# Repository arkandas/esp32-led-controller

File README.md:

# ESP32 LED Controller 💡

A custom ESP32-based controller for WS2812B/SK6812/WS2814 LED strips with web interface and Alexa integration.

> **Latest Version:** V2 includes 24V RGBW support (WS2814), temperature/humidity monitoring, and enhanced status LEDs.

## Versions

### Version 2
✅ Released - Latest version in `main` branch

### Version 1
✅ Released - Tagged as `v1.0.0`

---

## Version 2 Documentation

The following documentation applies to **Version 2** of the project. All files are located in the `v2/` directory.

### ✨ Features

- 🎨 **Web Interface** - Real-time control with environment monitoring
- 🗣️ **Alexa Integration** - Voice control support
- 🔘 **Physical Buttons** - Manual brightness/mode control
- 🌈 **Multiple Effects** - Rainbow, chase, breathing animations
- 📱 **Custom Colors** - Full RGBW color picker
- 🌡️ **Temperature & Humidity** - AHT20 sensor for environment monitoring
- 💡 **Status LEDs** - 3x RGB status indicators (Power, WiFi, Strip)
- ⚡ **24V RGBW Support** - WS2814 LED strips with dedicated white channel

### 📁 Project Structure

```
v2/
├── code/                      # Arduino code & web interface
│   └── esp32-ws2814/          # WS2814 (RGBW) version
│       ├── data/              # Web interface files
│       │   ├── index.html     # Main web UI
│       │   ├── style.css      # Styling
│       │   └── app.js         # JavaScript controls
│       └── esp32-ws2814.ino   # Arduino sketch
├── kicad/                     # KiCad PCB project files
└── assets/                    # Board photos & schematics
```

### 🚀 Quick Start

#### Prerequisites

1. **Arduino IDE** with ESP32 support
2. **Required Libraries:**
   - Adafruit NeoPixel (for WS2814 RGBW)
   - FastLED (for status LEDs)
   - FauxmoESP (Alexa integration)
   - AsyncTCP & ESPAsyncWebServer (ESP32 versions)
   - LittleFS (file system)
   - Adafruit AHTX0 (temperature sensor)

#### Installation

1. **Add ESP32 Board Support:**
   ```
   File → Preferences → Additional Board Manager URLs:
   https://raw.githubusercontent.com/espressif/arduino-esp32/gh-pages/package_esp32_index.json
   ```

2. **Board Configuration:**
   - Board: "ESP32S3 Dev Module"
   - Flash Size: "8MB"
   - Partition Scheme: "8M with spiffs (3MB APP/1.5MB SPIFFS)"

3. **Install Libraries** via Library Manager

#### Upload Process

1. **Configure Settings** in the `.ino` file:
   ```cpp
   const char* ssid = "Your_WiFi_Network";
   const char* password = "Your_WiFi_Password";
   #define DEVICE_NAME "Your_Alexa_Device_Name"
   #define WIFI_HOSTNAME "Your_Device_Hostname"
   #define WEB_SERVER_PORT 8080  // Your preferred port
   #define NUM_LEDS 60  // Your LED count
   ```

2. **Upload Web Files:**
   - Install [Arduino LittleFS Upload](https://github.com/earlephilhower/arduino-littlefs-upload) plugin
   - Place the `data` folder in your sketch directory
   - Use: Cmd + Shift + P, then select "Upload LittleFS to Pico/ESP8266/ESP32"

3. **Upload Arduino Sketch** normally

#### Programming via USB

The v2 board uses an **ESP32-S3** with built-in USB - no need for an external USB-to-serial adapter.

**USB Connection:**
- Connect a USB-C cable directly to the ESP32-S3's USB port
- The board will show up as a serial device on your computer

**Arduino IDE USB Configuration:**

To get USB UART working on the Serial Monitor:

1. **Board Settings (Tools menu):**
   - Board: `ESP32S3 Dev Module`
   - USB CDC On Boot: `Enabled` ⚠️ **Important for Serial Monitor**
   - USB Mode: `Hardware CDC and JTAG`
   - Upload Mode: `UART0 / Hardware CDC`
   - Flash Size: `8MB`
   - Partition Scheme: `8M with spiffs (3MB APP/1.5MB SPIFFS)`
   - Upload Speed: `921600` (or lower if uploads fail)

2. **Port Selection:**
   - After connecting USB, select the port showing as ESP32-S3 in Tools → Port
   - macOS: Usually appears as `/dev/cu.usbmodem*`
   - Windows: Usually appears as `COM*`
   - Linux: Usually appears as `/dev/ttyACM*`

**USB CDC On Boot Explained:**
- When `Enabled`, the Serial Monitor will work over USB immediately after boot
- This allows you to see debug output using `Serial.println()` without additional hardware
- The board will enumerate as a USB serial device (CDC - Communications Device Class)

**First-Time Programming:**
1. Connect the board via USB-C
2. The ESP32-S3 should automatically enter bootloader mode when uploading
3. If upload fails, try:
   - Press and hold the `BOOT` button (if available on your board)
   - Click Upload in Arduino IDE
   - Release `BOOT` button when upload starts
4. Open Serial Monitor (Ctrl/Cmd + Shift + M) at `115200` baud to see output

**Troubleshooting:**
- **Port not appearing:** Try a different USB cable (must support data, not just power)
- **Upload fails:** Lower the upload speed to `460800` or `115200`
- **Serial Monitor shows gibberish:** Ensure baud rate is set to `115200` and USB CDC On Boot is enabled

### 🔌 Hardware Connections

| ESP32 Pin | Connection |
|-----------|------------|
| GPIO 40   | WS2814 LED Strip Data |
| GPIO 41   | Status LEDs (3x SK6805-EC20) |
| GPIO 1    | I2C SCL (AHT20 Sensor) |
| GPIO 2    | I2C SDA (AHT20 Sensor) |
| GPIO 4-7  | Control Buttons |

### 🌐 Usage

After successful upload:

1. **WiFi Connection:** Status LEDs flash yellow (5x) when connected
2. **Web Interface:** Visit `http://[ESP32_IP]:8080` (or your configured port)

3. **Alexa:** Say "Alexa, turn on [your device name]"
4. **Buttons:** Physical controls for power/brightness/modes

### 🎛️ Controls

- **Power Button:** Long press (0.5s) to toggle on/off
- **Brightness:** ± buttons adjust in 10% steps
- **Mode Button:** Cycle through colors and effects
- **Web Interface:** Real-time RGBW control, effects, and environment monitoring

### 💡 Status LEDs

The board features 3 RGB status LEDs:
- **LED 1 (Power):** Always green when powered
- **LED 2 (WiFi):** Green when connected, Red when disconnected, Yellow during errors
- **LED 3 (Strip):** Green when strip is on, Red when off

### ⚡ Hardware

Custom PCB design includes:
- ESP32-S3-WROOM-1 (8MB Flash)
- SN74AHCT125 level shifter (3.3V → 5V for WS2814)
- LM1117S-3.3 voltage regulator
- 3x SK6805-EC20 RGB status LEDs
- AHT20 temperature & humidity sensor
- 4 control buttons
- 2.5mm barrel jack power input (24V for WS2814)

### 🔧 Key Differences from V1

- **RGBW Support:** Dedicated white channel for better white light quality
- **24V LED Strips:** Uses WS2814 instead of WS2812B/SK6812
- **Environment Monitoring:** Built-in AHT20 temperature and humidity sensor
- **Improved Status LEDs:** 3x addressable RGB LEDs instead of single common anode LED
- **Enhanced Web Interface:** Shows temperature, humidity, and more device information
- **Configurable Port:** Web server port can be customized

---

## Version 1 Documentation

The following documentation applies to **Version 1** of the project. All files are located in the `v1/` directory.

### ✨ Features

- 🎨 **Web Interface** - Real-time control via browser
- 🗣️ **Alexa Integration** - Voice control support
- 🔘 **Physical Buttons** - Manual brightness/mode control
- 🌈 **Multiple Effects** - Rainbow, chase, breathing animations
- 📱 **Custom Colors** - Full RGB color picker
- 🔧 **Two LED Types** - WS2812B (RGB) and SK6812 (RGBW) support

### 📁 Project Structure

```
v1/
├── code/                       # Arduino code & web interface
│   ├── esp32-ws2812b/          # WS2812B (RGB) version
│   │   ├── data/               # Web interface files
│   │   │   ├── index.html      # Main web UI
│   │   │   ├── style.css       # Styling
│   │   │   └── app.js          # JavaScript controls
│   │   └── esp32-ws2812b.ino   # Arduino sketch
│   └── esp32-sk6812/           # SK6812 (RGBW) version
│       ├── data/               # Web interface files
│       └── esp32-sk6812.ino    # Arduino sketch
├── kicad/                      # KiCad PCB project files
├── gerbers/                    # Manufacturing files
├── datasheets/                 # Component datasheets
├── ibom/                       # Interactive BOM
└── assets/                     # Board photos
```

### 🚀 Quick Start

#### Prerequisites

1. **Arduino IDE** with ESP32 support
2. **Required Libraries:**
   - FastLED (for WS2812B) or Adafruit NeoPixel (for SK6812)
   - FauxmoESP (Alexa integration)
   - AsyncTCP & ESPAsyncWebServer (ESP32 versions)
   - LittleFS (file system)

#### Installation

1. **Add ESP32 Board Support:**
   ```
   File → Preferences → Additional Board Manager URLs:
   https://raw.githubusercontent.com/espressif/arduino-esp32/gh-pages/package_esp32_index.json
   ```

2. **Board Configuration:**
   - Board: "ESP32S3 Dev Module"
   - Flash Size: "8MB"
   - Partition Scheme: "8M with spiffs (3MB APP/1.5MB SPIFFS)"

3. **Install Libraries** via Library Manager

4. **Choose Your LED Type:**
   - `v1/code/esp32-ws2812b/` for standard RGB strips
   - `v1/code/esp32-sk6812/` for RGBW strips with dedicated white channel

#### Upload Process

1. **Configure Settings** in the `.ino` file:
   ```cpp
   const char* ssid = "Your_WiFi_Network";
   const char* password = "Your_WiFi_Password";
   #define DEVICE_NAME "Bedroom Lights"
   #define NUM_LEDS 60  // Your LED count
   ```

2. **Upload Web Files:**
   - Install [Arduino LittleFS Upload](https://github.com/earlephilhower/arduino-littlefs-upload) plugin
   - Place the `data` folder in your sketch directory
   - Use: Cmd + Shift + P, then select "Upload LittleFS to Pico/ESP8266/ESP32"

3. **Upload Arduino Sketch** normally

### 🔌 Hardware Connections

| ESP32 Pin | Connection |
|-----------|------------|
| GPIO 2    | LED Strip Data |
| GPIO 17   | Status LED (Red) |
| GPIO 16   | Status LED (Green) |
| GPIO 18   | Status LED (Blue) |
| GPIO 4-7  | Control Buttons |

### 🌐 Usage

After successful upload:

1. **WiFi Connection:** Board flashes blue → yellow (5x) when connected
2. **Web Interface:** Visit `http://[ESP32_IP]:8080`

3. **Alexa:** Say "Alexa, turn on bedroom lights"
4. **Buttons:** Physical controls for power/brightness/modes

### 🎛️ Controls

- **Power Button:** Long press (0.5s) to toggle on/off
- **Brightness:** ± buttons adjust in 10% steps
- **Mode Button:** Cycle through colors and effects
- **Web Interface:** Real-time RGB control and effects

### 📖 Blog Post

Read the full build story and PCB design process for V1: [ESP32 LED Controller](https://arkandas.com/blog/esp32_led_controller)

### ⚡ Hardware

Custom PCB design includes:
- ESP32-S3-WROOM-1 (8MB Flash)
- SN74AHCT125 level shifter (3.3V → 5V)
- LM1117S-3.3 voltage regulator
- Common anode status LED
- 4 control buttons
- 2.5mm barrel jack power input

### 🛠️ Development

The web interface uses vanilla JavaScript with no external dependencies. All files are served from ESP32's LittleFS for fast loading and offline operation.

## 📄 License

This project is licensed under the MIT License - see the [LICENSE](LICENSE) file for details.

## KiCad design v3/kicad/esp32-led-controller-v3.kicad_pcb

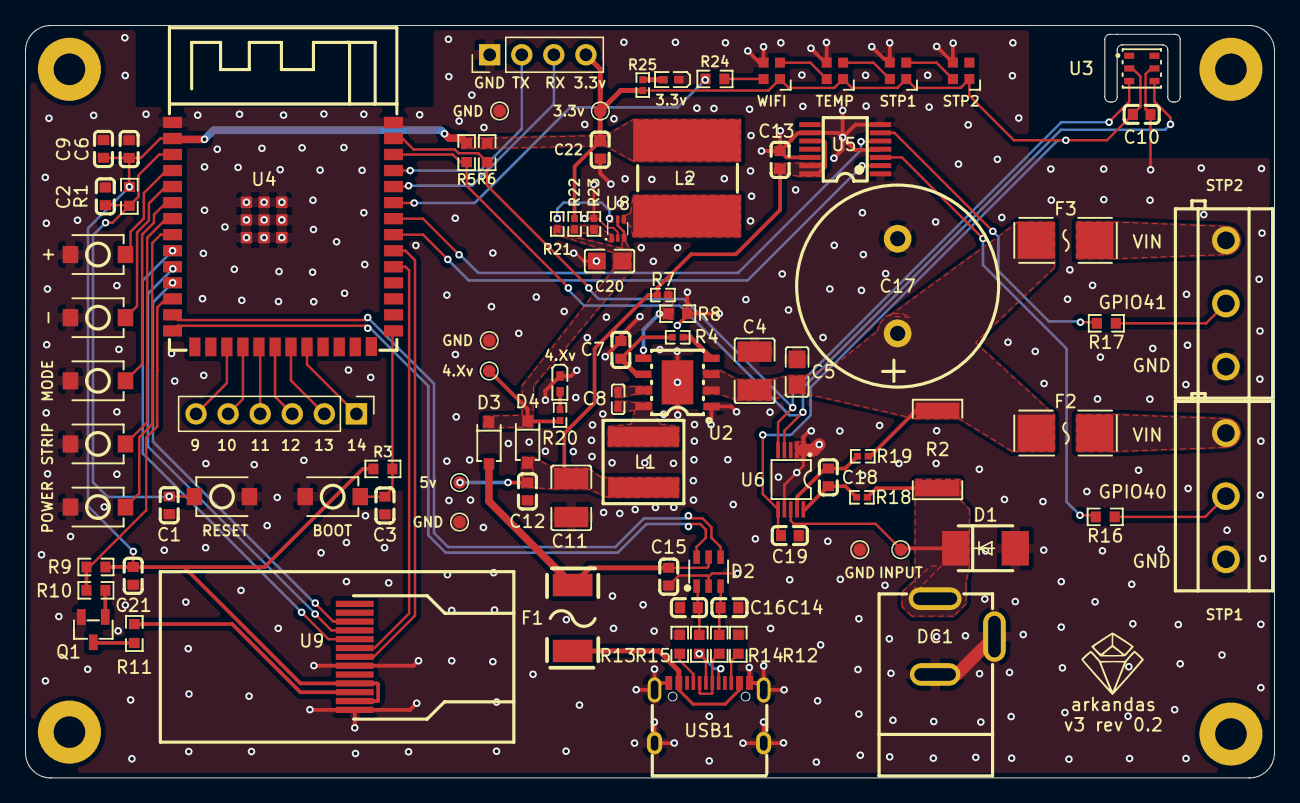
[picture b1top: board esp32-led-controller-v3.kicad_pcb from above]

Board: 2 copper layers, 98.9 x 59.6 mm, 95 parts (0 on the bottom side), 67 nets.

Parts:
3.3v: 3.3v; TestPoint_Pad_D1.0mm
3.3v#2, 4.Xv#2: GREEN_PWR; LED0402-R-RD_GREEN
4.Xv: 4.Xv; TestPoint_Pad_D1.0mm
5v: 5v; TestPoint_Pad_D1.0mm
+: +; SW-SMD_L3.9-W3.0-P4.45
-: -; SW-SMD_L3.9-W3.0-P4.45
C1, C3, C9, C10, C12, C13, C15, C18, C19, C21: 0.1uF; C0603
C2, C7: 1uF; C0603
C4: 10uF; C1210
C5: 220nF; C0805
C6: 10uF; C0603
C8: 0.1uF; C0402
C11: 47uF; C1210
C14, C16: 22pf; C0603
C17: 1000uF; CAP-TH_BD16.0-P7.50-D1.2-FD
C20: 4.7uF; C0805
C22: 22uF; C0603
D1: SMBJ26A; SMB_L4.4-W3.6-LS5.3-L-RD
D2: USBLC6-2SC6; SOT-23-6_L2.9-W1.6-P0.95-LS2.8-BL
D3, D4: B5819W; SOD-123_L2.7-W1.7-LS3.8-RD
DC1: DC-005-5A-2.5; DC-IN-TH_DC-005-5A-2.5
F1: 1.1A; FUSE-SMD_L4.7-W3.4
F2, F3: 5A Fuse; FUSE-SMD_L6.1-W2.7
GND: GND; TestPoint_Pad_D1.0mm
GND#2, GND#3, GND#4: GND; TestPoint_Pad_D1.0mm
H1, H2, H3, H4: MountingHole; MountingHole_2.5mm_Pad
INPUT: 5-24v; TestPoint_Pad_D1.0mm
J1, J2: KF301-5.0-3P; CONN-TH_3P-P5.00_KF301-5.0-3P
J3: UART; PinHeader_1x04_P2.54mm_Vertical
J4: GPIO; PinHeader_1x06_P2.54mm_Vertical
L1: 10uH; IND-SMD_L6.6-W6.4
L2: 1uH; IND-SMD_L8.2-W7.9
MODE: MODE; SW-SMD_L3.9-W3.0-P4.45
POWER: POWER; SW-SMD_L3.9-W3.0-P4.45
Q1: MMBT2222ALT1G; SOT-23-3_L2.9-W1.3-P1.90-LS2.4-BR
R1, R3, R9: 10K; R0603
R2: 20mOhm; R2512
R4, R7, R23: 100K; R0402
R5, R6: 4.7k; R0603
R8: 24.9K; R0603
R10: 1K; R0603
R11: 22ohm; R0603
R12, R13: 5.1K; R0603
R14, R15: 27ohm; R0603
R16, R17, R24: 100ohm; R0603
R18, R19: 10ohm; R0402
R20: 1.2Kohm; R0402
R21: 475K; R0402
R22: 453K; R0402
R25: 330ohm; R0402
STP1: STP1; LED-SMD_4P-L2.0-W2.0-BR
STP2: STP2; LED-SMD_4P-L2.0-W2.0-BR
STRIP: STRIP; SW-SMD_L3.9-W3.0-P4.45
SW4: RESET; SW-SMD_L3.9-W3.0-P4.45
SW5: BOOT; SW-SMD_L3.9-W3.0-P4.45
TEMP: TEMP; LED-SMD_4P-L2.0-W2.0-BR
U2: LMR33630ADDAR; ESOP-8_L4.9-W3.9-P1.27-LS6.0-TL-EP
U3: AHT20_C2757850; SENSOR-SMD_L3.0-W3.0-P1.00-BR
U4: ESP32-S3-WROOM-1(N16R8); WIRELM-SMD_ESP32-S3-WROOM-1
U5: SN74AHCT125PWR; TSSOP-14_L5.0-W4.4-P0.65-LS6.4-BL
U6: INA238AIDGSR; VSSOP-10_L3.0-W3.0-P0.50-LS4.9-BL
U8: TLV62569APDRLR; SOT-563_L1.6-W1.2-P0.50-LS1.6-BR
U9: HS096T01H13; LCD-SMD_HS096T01H13
USB1: TYPE-C 16PIN 2MD(073); USB-C-SMD_TYPE-C-6PIN-2MD-073
WIFI: WIFI; LED-SMD_4P-L2.0-W2.0-BR

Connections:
+3.3V: 3.3v.1 (1_1), C6.1, C9.1, C10.1, C19.1, C21.1, C22.1, J3.4, L2.2, R1.1, R3.1, R5.1, R6.1, R9.1, R22.1, R25.1, STP1.1 (VDD), STP2.1 (VDD), TEMP.1 (VDD), U3.2 (VDD), U4.2 (3V3), U6.6 (VS), U9.10 (VCC), U9.12 (LEDA), WIFI.1 (VDD)
/USB_VD+: R15.1, USB1.6 (DP1), USB1.8 (DP2)
/USB_VD-: R14.1, USB1.5 (DN2), USB1.7 (DN1)
BOOT: C3.1, R3.2, SW5.1, U4.27 (IO0)
CHIP_PU: C1.1, C2.1, R1.2, SW4.1, U4.3 (EN)
GND: 3.3v#2.2 (K), 4.Xv#2.2 (K), +.2, -.2, C1.2, C2.2, C3.2, C4.2, C5.2, C6.2, C7.2, C9.2, C10.2, C11.2, C12.2, C13.2, C14.2, C15.2, C16.2, C17.2, C19.2, C20.2, C21.2, C22.2, D1.2 (A), D2.2, DC1.2, DC1.3, GND.1 (1_1), GND#2.1 (1_1), GND#3.1 (1_1), GND#4.1 (1_1), J1.1, J2.1, J3.1, MODE.2, POWER.2, Q1.2 (E), R8.2, R12.2, R13.2, R23.2, STP1.3 (GND), STP2.3 (GND), STRIP.2, SW4.2, SW5.2, TEMP.3 (GND), U2.1 (PGND), U2.9 (EP), U3.5 (GND), U4.1 (GND), U4.40 (GND), U4.41 (GND), U5.1 (~1OE), U5.4 (~2OE), U5.7 (GND), U5.9 (3A), U5.12 (4A), U6.1 (A1), U6.2 (A0), U6.7 (GND), U8.2 (GND), U9.8 (GND), U9.13 (GND), USB1.1 (GND), USB1.12 (GND), USB1.13 (SHELL), USB1.14 (SHELL), WIFI.3 (GND)
IN+: D1.1 (K), DC1.1, INPUT.1 (1_1), R2.1, R18.2, U6.8 (VBUS)
IN-: C4.1, C5.1, C17.1, F2.1, F3.1, R2.2, R19.2, U2.2 (VIN), U2.3 (EN)
IO4: +.1, U4.4 (IO4)
IO5: -.1, U4.5 (IO5)
IO6: MODE.1, U4.6 (IO6)
IO7: STRIP.1, U4.7 (IO7)
IO9: J4.6, U4.17 (IO9)
IO10: J4.5, U4.18 (IO10)
IO11: J4.4, U4.19 (IO11)
IO12: J4.3, U4.20 (IO12)
IO13: J4.2, U4.21 (IO13)
IO14: J4.1, U4.22 (IO14)
IO15: POWER.1, U4.8 (IO15)
IO40: U4.33 (IO40), U5.2 (1A)
IO41: U4.34 (IO41), U5.5 (2A)
IO42: R24.2, U4.35 (IO42)
LCD_BACKLIGHT: R9.2, R10.1, U4.12 (IO8)
LCD_CS: U4.32 (IO39), U9.7 (CS)
LCD_DC: U4.9 (IO16), U9.5 (RS)
LCD_MOSI: U4.11 (IO18), U9.3 (SDA)
LCD_RST: U4.31 (IO38), U9.6 (RES)
LCD_SCLK: U4.10 (IO17), U9.4 (SCL)
LEDK: R11.1, U9.11 (LEDK)
LED_STRIP: R17.1, U5.6 (2Y)
LED_STRIP_2: R16.1, U5.3 (1Y)
unnamed: 4.Xv.1 (1_1), C20.1, D3.1 (C), D4.1 (C), R20.2, R21.2, U8.3 (VIN), U8.5 (EN)
unnamed: F1.1, USB1.2 (VBUS), USB1.11 (VBUS)
unnamed: F2.2, J1.3
unnamed: F3.2, J2.3
unnamed: J1.2, R16.2
unnamed: J2.2, R17.2
unnamed: STP1.2 (DOUT), STP2.4 (DIN)
unnamed: STP1.4 (DIN), TEMP.2 (DOUT)
unnamed: 4.Xv#2.1 (A), R20.1
unnamed: TEMP.4 (DIN), WIFI.2 (DOUT)
unnamed: R24.1, WIFI.4 (DIN)
unnamed: 3.3v#2.1 (A), R25.2
unnamed: Q1.1 (B), R10.2
unnamed: Q1.3 (C), R11.2
unnamed: C8.1, U2.7 (BOOT)
unnamed: R7.2, R8.1, U2.5 (FB)
unnamed: R4.1, U2.4 (PG)
unnamed: C8.2, L1.1, U2.8 (SW)
unnamed: C7.1, R4.2, U2.6 (VCC)
unnamed: C18.1, R18.1, U6.10 (IN+)
unnamed: C18.2, R19.1, U6.9 (IN-)
unnamed: R22.2, R23.1, U8.1 (FB)
unnamed: R21.1, U8.6 (NC/PG)
unnamed: L2.1, U8.4 (SW)
unnamed: R13.1, USB1.4 (CC1)
unnamed: R12.1, USB1.10 (CC2)
RX: J3.3, U4.36 (RXD0)
SCL: R6.2, U3.3 (SCL), U4.39 (IO1), U6.5 (SCL)
SDA: R5.2, U3.4 (SDA), U4.38 (IO2), U6.4 (SDA)
TX: J3.2, U4.37 (TXD0)
USB_DN: C14.1, D2.3, R14.2
USB_DON: D2.4, U4.13 (IO19)
USB_DOP: D2.6, U4.14 (IO20)
USB_DP: C16.1, D2.1, R15.2
VBUS: C15.1, D2.5, D3.2 (A), F1.2
VOUT5V: 5v.1 (1_1), C11.1, C12.1, C13.1, D4.2 (A), L1.2, R7.1, U5.10 (~3OE), U5.13 (~4OE), U5.14 (VCC)

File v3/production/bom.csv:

Designator,Footprint,Quantity,Value,LCSC Part #
+,SW-SMD_L3.9-W3.0-P4.45,1,+,C720477
-,SW-SMD_L3.9-W3.0-P4.45,1,-,C720477
3.3V_2,TestPoint_Pad_D1.0mm,1,3.3v,
"3.3V, 4.XV",LED0402-R-RD_GREEN,2,GREEN_PWR,C434446
4.XV_2,TestPoint_Pad_D1.0mm,1,4.Xv,
5V,TestPoint_Pad_D1.0mm,1,5v,
"C1, C10, C13, C18, C19, C21, C3, C9",C0603,8,0.1uF,C1591
C11,C1210,1,47uF,C77101
"C12, C15",C0603,2,0.1uF,C14663
"C14, C16",C0603,2,22pf,C1653
C17,CAP-TH_BD16.0-P7.50-D1.2-FD,1,1000uF,C383058
"C2, C7",C0603,2,1uF,C696361
C20,C0805,1,4.7uF,C1779
C22,C0603,1,22uF,C77042
C4,C1210,1,10uF,C77102
C5,C0805,1,220nF,C107131
C6,C0603,1,10uF,C96446
C8,C0402,1,0.1uF,C71629
D1,SMB_L4.4-W3.6-LS5.3-L-RD,1,SMBJ26A,C315992
D2,SOT-23-6_L2.9-W1.6-P0.95-LS2.8-BL,1,USBLC6-2SC6,C7519
"D3, D4",SOD-123_L2.7-W1.7-LS3.8-RD,2,B5819W,C5345968
DC1,DC-IN-TH_DC-005-5A-2.5,1,DC-005-5A-2.5,C381115
F1,FUSE-SMD_L4.7-W3.4,1,1.1A,C163516
"F2, F3",FUSE-SMD_L6.1-W2.7,2,5A Fuse,C66503
"GND_4, GND_3, GND_2, GND",TestPoint_Pad_D1.0mm,4,GND,
INPUT,TestPoint_Pad_D1.0mm,1,5-24v,
"J1, J2",CONN-TH_3P-P5.00_KF301-5.0-3P,2,KF301-5.0-3P,C474882
J3,PinHeader_1x04_P2.54mm_Vertical,1,UART,
J4,PinHeader_1x06_P2.54mm_Vertical,1,GPIO,
L1,IND-SMD_L6.6-W6.4,1,10uH,C5329540
L2,IND-SMD_L8.2-W7.9,1,1uH,C2041438
MODE,SW-SMD_L3.9-W3.0-P4.45,1,MODE,C720477
POWER,SW-SMD_L3.9-W3.0-P4.45,1,POWER,C720477
Q1,SOT-23-3_L2.9-W1.3-P1.90-LS2.4-BR,1,MMBT2222ALT1G,C82460
"R1, R3, R9",R0603,3,10K,C98220
R10,R0603,1,1K,C22548
R11,R0603,1,22ohm,C23345
"R12, R13",R0603,2,5.1K,C105580
"R14, R15",R0603,2,27ohm,C137753
"R16, R17, R24",R0603,3,100ohm,C105588
"R18, R19",R0402,2,10ohm,C2906862
R2,R2512,1,20mOhm,C2903469
R20,R0402,1,1.2Kohm,C2909307
R21,R0402,1,475K,C2085628
R22,R0402,1,453K,C843903
"R23, R4, R7",R0402,3,100K,C481918
R25,R0402,1,330ohm,C2930002
"R5, R6",R0603,2,4.7k,C99782
R8,R0603,1,24.9K,C137761
STP1,LED-SMD_4P-L2.0-W2.0-BR,1,STP1,C2890036
STP2,LED-SMD_4P-L2.0-W2.0-BR,1,STP2,C2890036
STRIP,SW-SMD_L3.9-W3.0-P4.45,1,STRIP,C720477
SW4,SW-SMD_L3.9-W3.0-P4.45,1,RESET,C720477
SW5,SW-SMD_L3.9-W3.0-P4.45,1,BOOT,C720477
TEMP,LED-SMD_4P-L2.0-W2.0-BR,1,TEMP,C2890036
U2,ESOP-8_L4.9-W3.9-P1.27-LS6.0-TL-EP,1,LMR33630ADDAR,C841384
U3,SENSOR-SMD_L3.0-W3.0-P1.00-BR,1,AHT20_C2757850,C2757850
U4,WIRELM-SMD_ESP32-S3-WROOM-1,1,ESP32-S3-WROOM-1(N16R8),C2913202
U5,TSSOP-14_L5.0-W4.4-P0.65-LS6.4-BL,1,SN74AHCT125PWR,C36365
U6,VSSOP-10_L3.0-W3.0-P0.50-LS4.9-BL,1,INA238AIDGSR,C2868250
U8,SOT-563_L1.6-W1.2-P0.50-LS1.6-BR,1,TLV62569APDRLR,C398366
U9,LCD-SMD_HS096T01H13,1,HS096T01H13,C18198246
USB1,USB-C-SMD_TYPE-C-6PIN-2MD-073,1,TYPE-C 16PIN 2MD(073),C2765186
WIFI,LED-SMD_4P-L2.0-W2.0-BR,1,WIFI,C2890036

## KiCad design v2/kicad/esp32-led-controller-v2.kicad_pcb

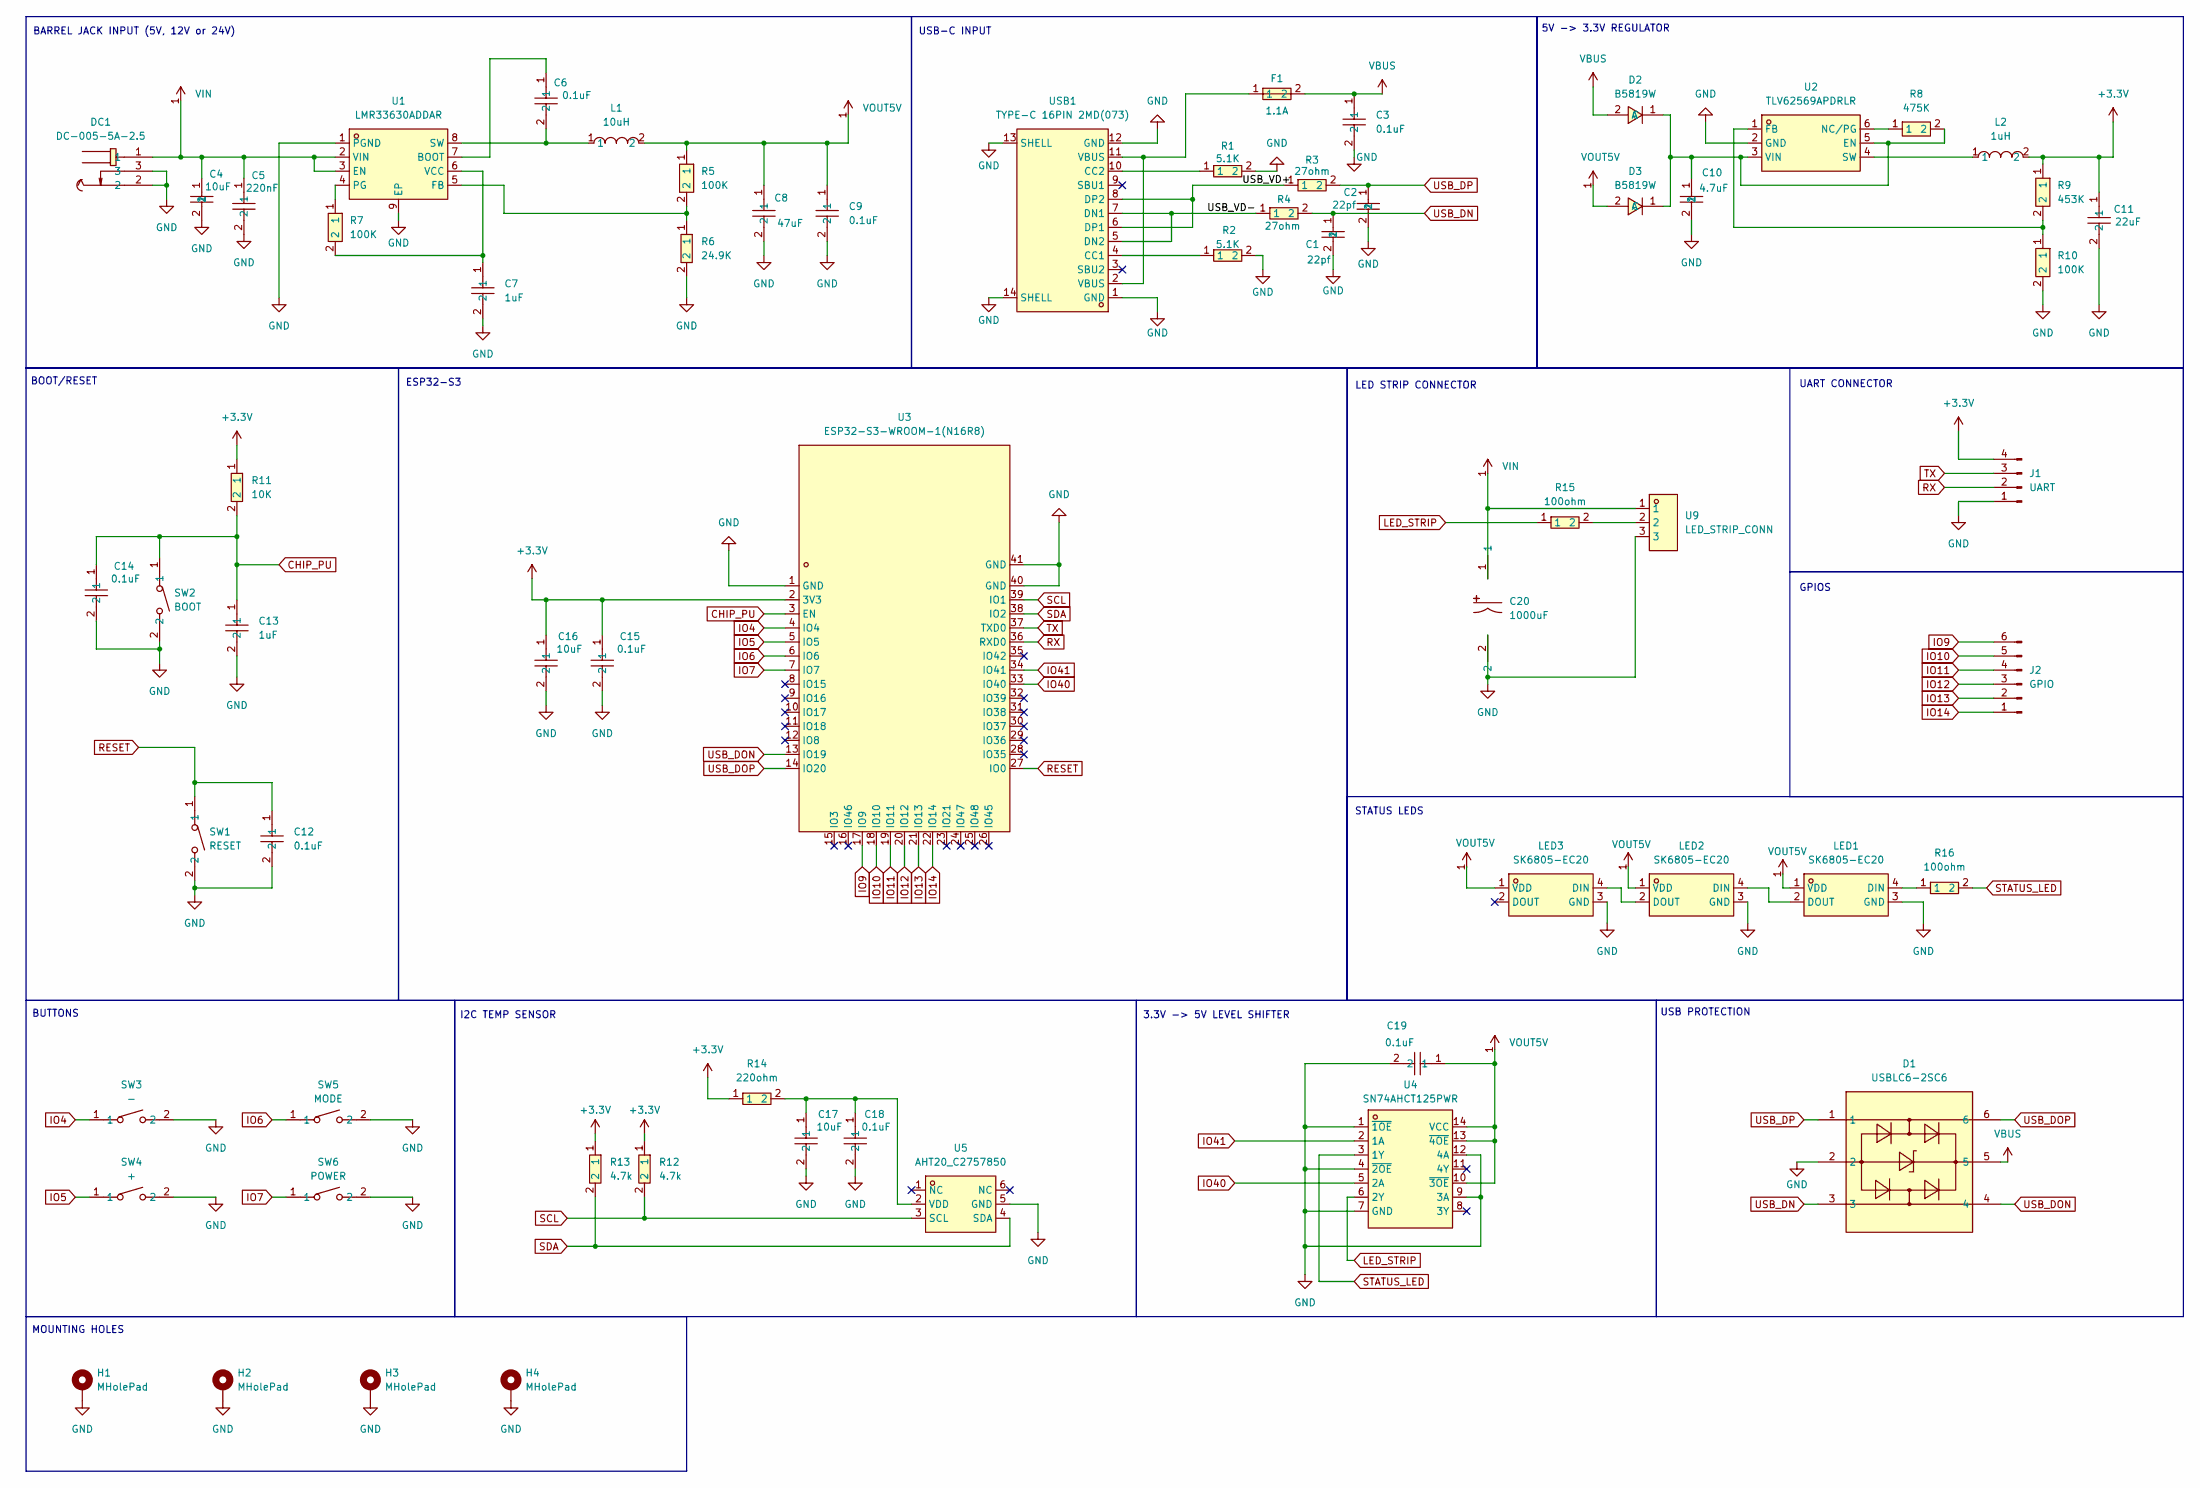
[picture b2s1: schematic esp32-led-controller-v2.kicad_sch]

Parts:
C1, C2: 22pf; C0603; LCSC Part C1653
C3, C9: 0.1uF; C0603; LCSC Part C14663
C4: 10uF; C1210; LCSC Part C77102
C5: 220nF; C0805; LCSC Part C107131
C6: 0.1uF; C0402; LCSC Part C71629
C7: 1uF; C0603; LCSC Part C696361
C8: 47uF; C1210; LCSC Part C77101
C10: 4.7uF; C0805; LCSC Part C1779
C11: 22uF; C0603; LCSC Part C77042
C12, C14, C15, C18, C19: 0.1uF; C0603; LCSC Part C1591
C13: 1uF; C0603; LCSC Part C2918486
C16, C17: 10uF; C0603; LCSC Part C96446
C20: 1000uF; CAP-TH_BD16.0-P7.50-D1.2-FD; LCSC Part C383058
D1: USBLC6-2SC6; SOT-23-6_L2.9-W1.6-P0.95-LS2.8-BL; LCSC Part C7519
D2, D3: B5819W; SOD-123_L2.7-W1.7-LS3.8-RD; LCSC Part C5345968
DC1: DC-005-5A-2.5; DC-IN-TH_DC-005-5A-2.5; LCSC Part C381115
F1: 1.1A; FUSE-SMD_L4.7-W3.4; LCSC Part C163516
H1, H2, H3, H4: MHolePad; MountingHole_3.2mm_M3_Pad_Via
J1: UART; PinHeader_1x04_P2.54mm_Vertical
J2: GPIO; PinHeader_1x06_P2.54mm_Vertical
L1: 10uH; IND-SMD_L6.6-W6.4; LCSC Part C5329540
L2: 1uH; IND-SMD_L8.2-W7.9; LCSC Part C2041438
LED1, LED2, LED3: SK6805-EC20; LED-SMD_4P-L2.0-W2.0-BR; LCSC Part C2890036
R1, R2: 5.1K; R0603; LCSC Part C105580
R3, R4: 27ohm; R0603; LCSC Part C137753
R5, R7, R10: 100K; R0402; LCSC Part C481918
R6: 24.9K; R0603; LCSC Part C137761
R8: 475K; R0402; LCSC Part C2085628
R9: 453K; R0402; LCSC Part C843903
R11: 10K; R0603; LCSC Part C25804
R12, R13: 4.7k; R0603; LCSC Part C99782
R14: 220ohm; R0603; LCSC Part C22962
R15, R16: 100ohm; R0603; LCSC Part C105588
SW1: RESET; SW-SMD_L3.9-W3.0-P4.45; LCSC Part C720477
SW2: BOOT; SW-SMD_L3.9-W3.0-P4.45; LCSC Part C720477
SW3: -; SW-SMD_L3.9-W3.0-P4.45; LCSC Part C720477
SW4: +; SW-SMD_L3.9-W3.0-P4.45; LCSC Part C720477
SW5: MODE; SW-SMD_L3.9-W3.0-P4.45; LCSC Part C720477
SW6: POWER; SW-SMD_L3.9-W3.0-P4.45; LCSC Part C720477
U1: LMR33630ADDAR; ESOP-8_L4.9-W3.9-P1.27-LS6.0-TL-EP; LCSC Part C841384
U2: TLV62569APDRLR; SOT-563_L1.6-W1.2-P0.50-LS1.6-BR; LCSC Part C398366
U3: ESP32-S3-WROOM-1(N16R8); WIRELM-SMD_ESP32-S3-WROOM-1; LCSC Part C2913202
U4: SN74AHCT125PWR; TSSOP-14_L5.0-W4.4-P0.65-LS6.4-BL; LCSC Part C36365
U5: AHT20_C2757850; SENSOR-SMD_L3.0-W3.0-P1.00-BR; LCSC Part C2757850
U9: LED_STRIP_CONN; CONN-TH_3P-P5.00_KF301-5.0-3P; LCSC Part C474882
USB1: TYPE-C 16PIN 2MD(073); USB-C-SMD_TYPE-C-6PIN-2MD-073; LCSC Part C2765186

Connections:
+3.3V: C11.1, C15.1, C16.1, J1.4, L2.2, R9.1, R11.1, R12.1, R13.1, R14.1, U3.2 (3V3)
/USB_VD+: R3.1, USB1.6 (DP1), USB1.8 (DP2)
/USB_VD-: R4.1, USB1.5 (DN2), USB1.7 (DN1)
CHIP_PU: C13.1, C14.1, R11.2, SW2.1, U3.3 (EN)
GND: C1.2, C2.2, C3.2, C4.2, C5.2, C7.2, C8.2, C9.2, C10.2, C11.2, C12.2, C13.2, C14.2, C15.2, C16.2, C17.2, C18.2, C19.2, C20.2, D1.2, DC1.2, DC1.3, H1.1, H2.1, H3.1, H4.1, J1.1, LED1.3 (GND), LED2.3 (GND), LED3.3 (GND), R1.2, R2.2, R6.2, R10.2, SW1.2, SW2.2, SW3.2, SW4.2, SW5.2, SW6.2, U1.1 (PGND), U1.9 (EP), U2.2 (GND), U3.1 (GND), U3.40 (GND), U3.41 (GND), U4.1 (~1OE), U4.4 (~2OE), U4.7 (GND), U4.9 (3A), U4.12 (4A), U5.5 (GND), U9.3, USB1.1 (GND), USB1.12 (GND), USB1.13 (SHELL), USB1.14 (SHELL)
IO4: SW3.1, U3.4 (IO4)
IO5: SW4.1, U3.5 (IO5)
IO6: SW5.1, U3.6 (IO6)
IO7: SW6.1, U3.7 (IO7)
IO9: J2.6, U3.17 (IO9)
IO10: J2.5, U3.18 (IO10)
IO11: J2.4, U3.19 (IO11)
IO12: J2.3, U3.20 (IO12)
IO13: J2.2, U3.21 (IO13)
IO14: J2.1, U3.22 (IO14)
IO40: U3.33 (IO40), U4.5 (2A)
IO41: U3.34 (IO41), U4.2 (1A)
LED_STRIP: R15.1, U4.6 (2Y)
unnamed: C10.1, D2.1 (C), D3.1 (C), R8.2, U2.3 (VIN), U2.5 (EN)
unnamed: F1.1, USB1.2 (VBUS), USB1.11 (VBUS)
unnamed: LED1.4 (DIN), R16.1
unnamed: LED1.2 (DOUT), LED2.4 (DIN)
unnamed: LED2.2 (DOUT), LED3.4 (DIN)
unnamed: R15.2, U9.2
unnamed: C6.1, U1.7 (BOOT)
unnamed: R5.2, R6.1, U1.5 (FB)
unnamed: R7.1, U1.4 (PG)
unnamed: C6.2, L1.1, U1.8 (SW)
unnamed: C7.1, R7.2, U1.6 (VCC)
unnamed: R9.2, R10.1, U2.1 (FB)
unnamed: R8.1, U2.6 (NC/PG)
unnamed: L2.1, U2.4 (SW)
unnamed: C17.1, C18.1, R14.2, U5.2 (VDD)
unnamed: R2.1, USB1.4 (CC1)
unnamed: R1.1, USB1.10 (CC2)
RESET: C12.1, SW1.1, U3.27 (IO0)
RX: J1.2, U3.36 (RXD0)
SCL: R12.2, U3.39 (IO1), U5.3 (SCL)
SDA: R13.2, U3.38 (IO2), U5.4 (SDA)
STATUS_LED: R16.2, U4.3 (1Y)
TX: J1.3, U3.37 (TXD0)
USB_DN: C1.1, D1.3, R4.2
USB_DON: D1.4, U3.13 (IO19)
USB_DOP: D1.6, U3.14 (IO20)
USB_DP: C2.1, D1.1, R3.2
VBUS: C3.1, D1.5, D2.2 (A), F1.2
VIN: C4.1, C5.1, C20.1, DC1.1, U1.2 (VIN), U1.3 (EN), U9.1
VOUT5V: C8.1, C9.1, C19.1, D3.2 (A), L1.2, LED1.1 (VDD), LED2.1 (VDD), LED3.1 (VDD), R5.1, U4.10 (~3OE), U4.13 (~4OE), U4.14 (VCC)

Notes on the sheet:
MOUNTING HOLES
BOOT/RESET
3.3V -> 5V LEVEL SHIFTER
ESP32-S3
GPIOS
LED STRIP CONNECTOR
I2C TEMP SENSOR
BUTTONS
USB PROTECTION
UART CONNECTOR
BARREL JACK INPUT (5V, 12V or 24V)
5V -> 3.3V REGULATOR
USB-C INPUT
STATUS LEDS

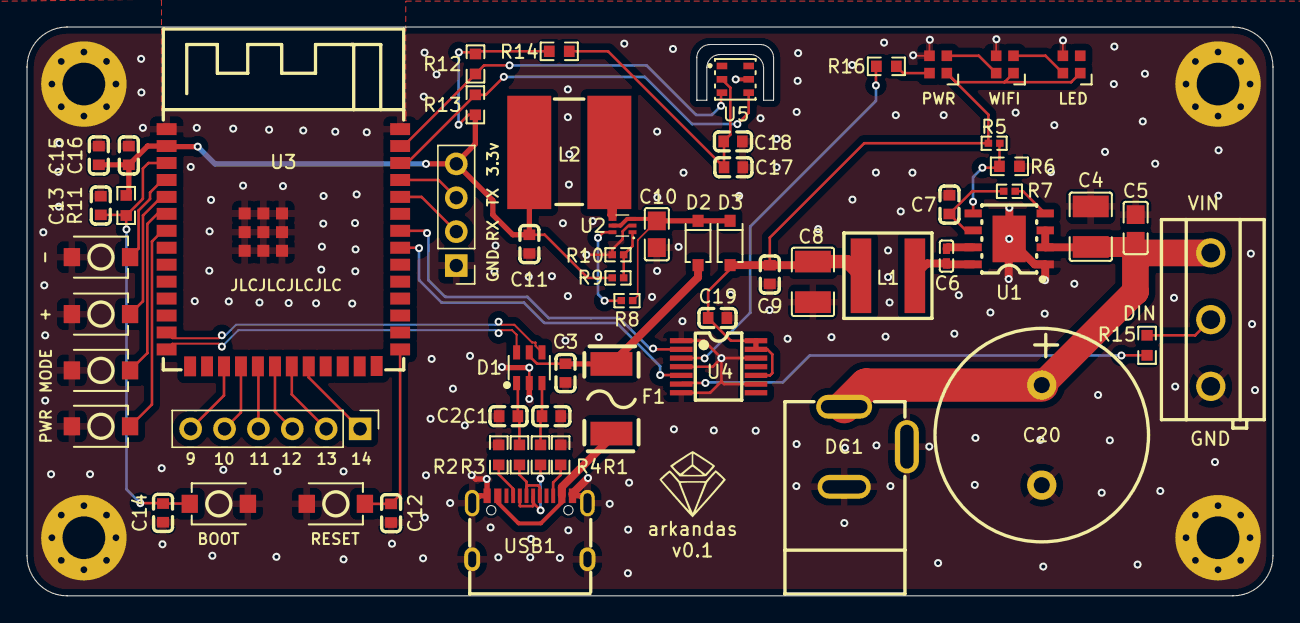
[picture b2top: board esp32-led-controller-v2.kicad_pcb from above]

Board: 2 copper layers, 93.4 x 42.6 mm, 65 parts (0 on the bottom side), 48 nets.

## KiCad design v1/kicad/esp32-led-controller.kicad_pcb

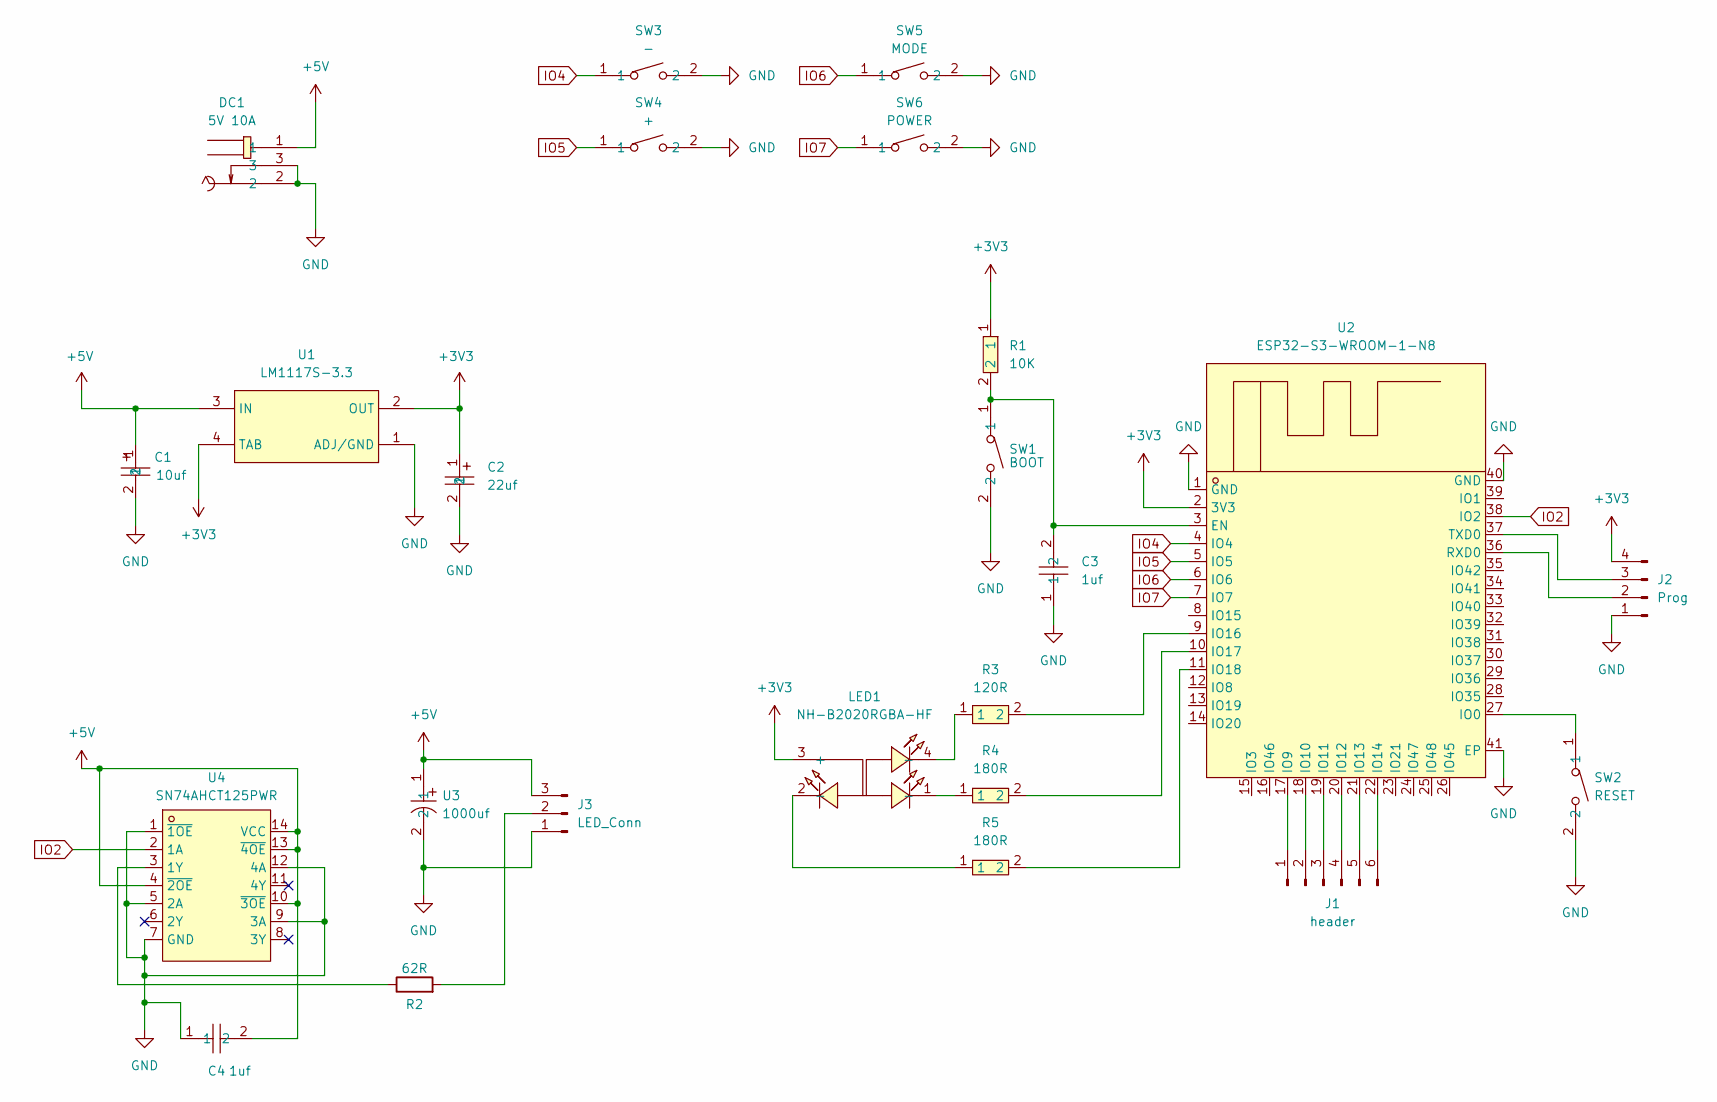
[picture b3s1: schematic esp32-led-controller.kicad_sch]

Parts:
C1: 10uf; CAP-SMD_L3.2-W1.6-RD-C7171; LCSC Part C7171
C2: 22uf; CASE-A_3216; LCSC Part C11366
C3, C4: 1uf; C0603; LCSC Part C2918486
DC1: 5V 10A; DC-IN-TH_DC-005-5A-2.5; LCSC Part C381115
J1: header; PinHeader_1x06_P2.54mm_Vertical
J2: Prog; PinHeader_1x04_P2.54mm_Vertical
J3: LED_Conn; TerminalBlock_MaiXu_MX126-5.0-03P_1x03_P5.00mm
LED1: NH-B2020RGBA-HF; LED-ARRAY-SMD_4P-L2.1-W2.1-TL_NH-B2020RGBA; LCSC Part C2874116
R1: 10K; R0603; LCSC Part C25804
R2: 62R; R_1206_3216Metric; LCSC Part C3013271
R3: 120R; R0603; LCSC Part C2907096
R4, R5: 180R; R0603; LCSC Part C22828
SW1: BOOT; SW-SMD_L3.9-W3.0-P4.45; LCSC Part C720477
SW2: RESET; SW-SMD_L3.9-W3.0-P4.45; LCSC Part C720477
SW3: -; SW-SMD_L3.9-W3.0-P4.45; LCSC Part C720477
SW4: +; SW-SMD_L3.9-W3.0-P4.45; LCSC Part C720477
SW5: MODE; SW-SMD_L3.9-W3.0-P4.45; LCSC Part C720477
SW6: POWER; SW-SMD_L3.9-W3.0-P4.45; LCSC Part C720477
U1: LM1117S-3.3; SOT-223-3_L6.5-W3.4-P2.30-LS7.0-BR; LCSC Part C126027
U2: ESP32-S3-WROOM-1-N8; WIFIM-SMD_ESP32-S3-WROOM-1-N8; LCSC Part C2913198
U3: 1000uf; CAP-SMD_BD8.0-L8.3-W8.3-LS9.1-FD; LCSC Part C19191929
U4: SN74AHCT125PWR; TSSOP-14_L5.0-W4.4-P0.65-LS6.4-BL; LCSC Part C36365

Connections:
+3V3: C2.1, J2.4, LED1.3 (+), R1.1, U1.2 (OUT), U1.4 (TAB), U2.2 (3V3)
+5V: C1.1, C4.2, DC1.1, J3.3, U1.3 (IN), U3.1, U4.4 (~2OE), U4.10 (~3OE), U4.13 (~4OE), U4.14 (VCC)
GND: C1.2, C2.2, C3.1, C4.1, DC1.2, DC1.3, J2.1, J3.1, SW1.2, SW2.2, SW3.2, SW4.2, SW5.2, SW6.2, U1.1 (ADJ/GND), U2.1 (GND), U2.40 (GND), U2.41 (EP), U3.2, U4.1 (~1OE), U4.5 (2A), U4.7 (GND), U4.9 (3A), U4.12 (4A)
IO2: U2.38 (IO2), U4.2 (1A)
IO4: SW3.1, U2.4 (IO4)
IO5: SW4.1, U2.5 (IO5)
IO6: SW5.1, U2.6 (IO6)
IO7: SW6.1, U2.7 (IO7)
unnamed: J1.1, U2.17 (IO9)
unnamed: J1.2, U2.18 (IO10)
unnamed: J1.3, U2.19 (IO11)
unnamed: J1.4, U2.20 (IO12)
unnamed: J1.5, U2.21 (IO13)
unnamed: J1.6, U2.22 (IO14)
unnamed: J2.2, U2.36 (RXD0)
unnamed: J2.3, U2.37 (TXD0)
unnamed: J3.2, R2.2
unnamed: LED1.1 (-), R4.1
unnamed: LED1.2 (-), R5.1
unnamed: LED1.4 (-), R3.1
unnamed: C3.2, R1.2, SW1.1, U2.3 (EN)
unnamed: SW2.1, U2.27 (IO0)
unnamed: R3.2, U2.9 (IO16)
unnamed: R4.2, U2.10 (IO17)
unnamed: R5.2, U2.11 (IO18)
unnamed: R2.1, U4.3 (1Y)

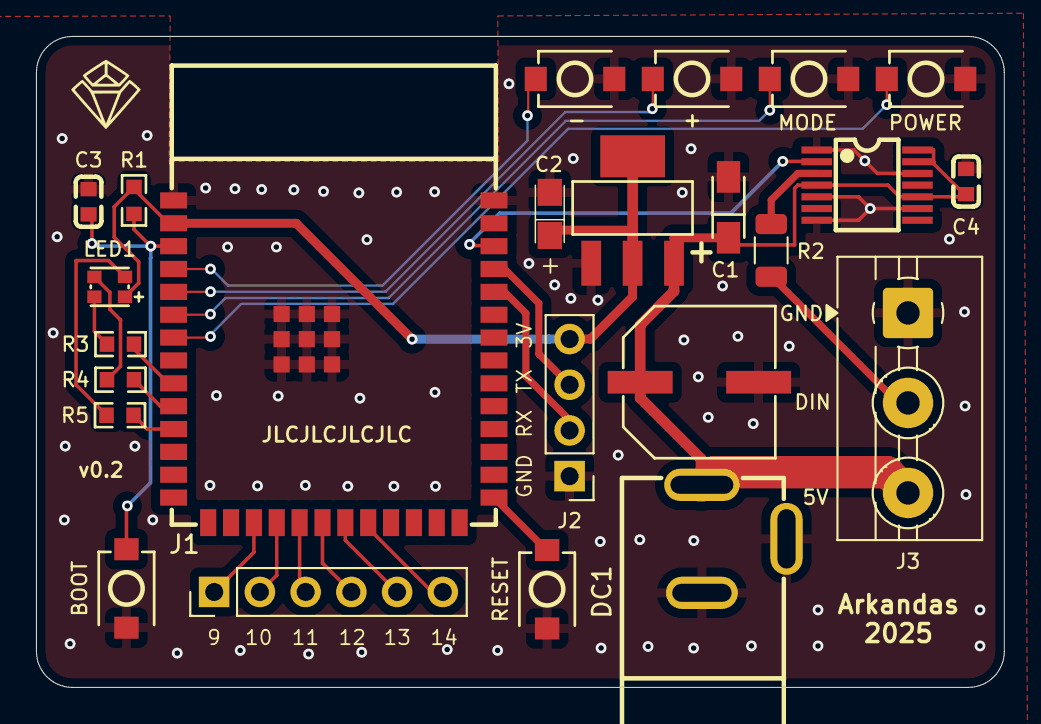
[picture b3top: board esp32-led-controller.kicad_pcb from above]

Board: 2 copper layers, 53.8 x 36.2 mm, 24 parts (0 on the bottom side), 26 nets.

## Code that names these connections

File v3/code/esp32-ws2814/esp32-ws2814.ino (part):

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#define LED_STRIP_PIN_2  41

// Status LEDs (4x SK6805-EC20 on IO42)
#define STATUS_LED_PIN 42
#define NUM_STATUS_LEDS 4
#define STATUS_LED_TYPE WS2812
#define STATUS_COLOR_ORDER GRB
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
// ST7735 LCD (SPI) — HS096T01H13, 0.96" 80×160 (LCSC C18198246)
// CLK/MOSI/DC are kept off the octal-PSRAM bus (GPIO35/36/37) so PSRAM stays usable.
#define LCD_CS   39
#define LCD_RST  38
#define LCD_DC   16
#define LCD_CLK  17
#define LCD_MOSI 18
#define LCD_BL   8

// INA238 power monitor
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  Serial.println("ESP32-S3 LED Controller V3 - Dual WS2814 RGBW & SK6805 Status LEDs");

  // Initialize status LEDs first for error indication
  FastLED.addLeds<STATUS_LED_TYPE, STATUS_LED_PIN, STATUS_COLOR_ORDER>(statusLeds, NUM_STATUS_LEDS);

  // Validate configuration
  if (String(ssid) == "your_wifi_ssid" || String(password) == "your_wifi_password") {
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
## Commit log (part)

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2025-07-27 First release
2025-10-30 v2 first revision
2026-02-09 Finished version 2.0.0
2026-02-09 Updated programming instructions for v2
2026-06-21 v3: board rev 2 + dual-strip firmware and web UI
